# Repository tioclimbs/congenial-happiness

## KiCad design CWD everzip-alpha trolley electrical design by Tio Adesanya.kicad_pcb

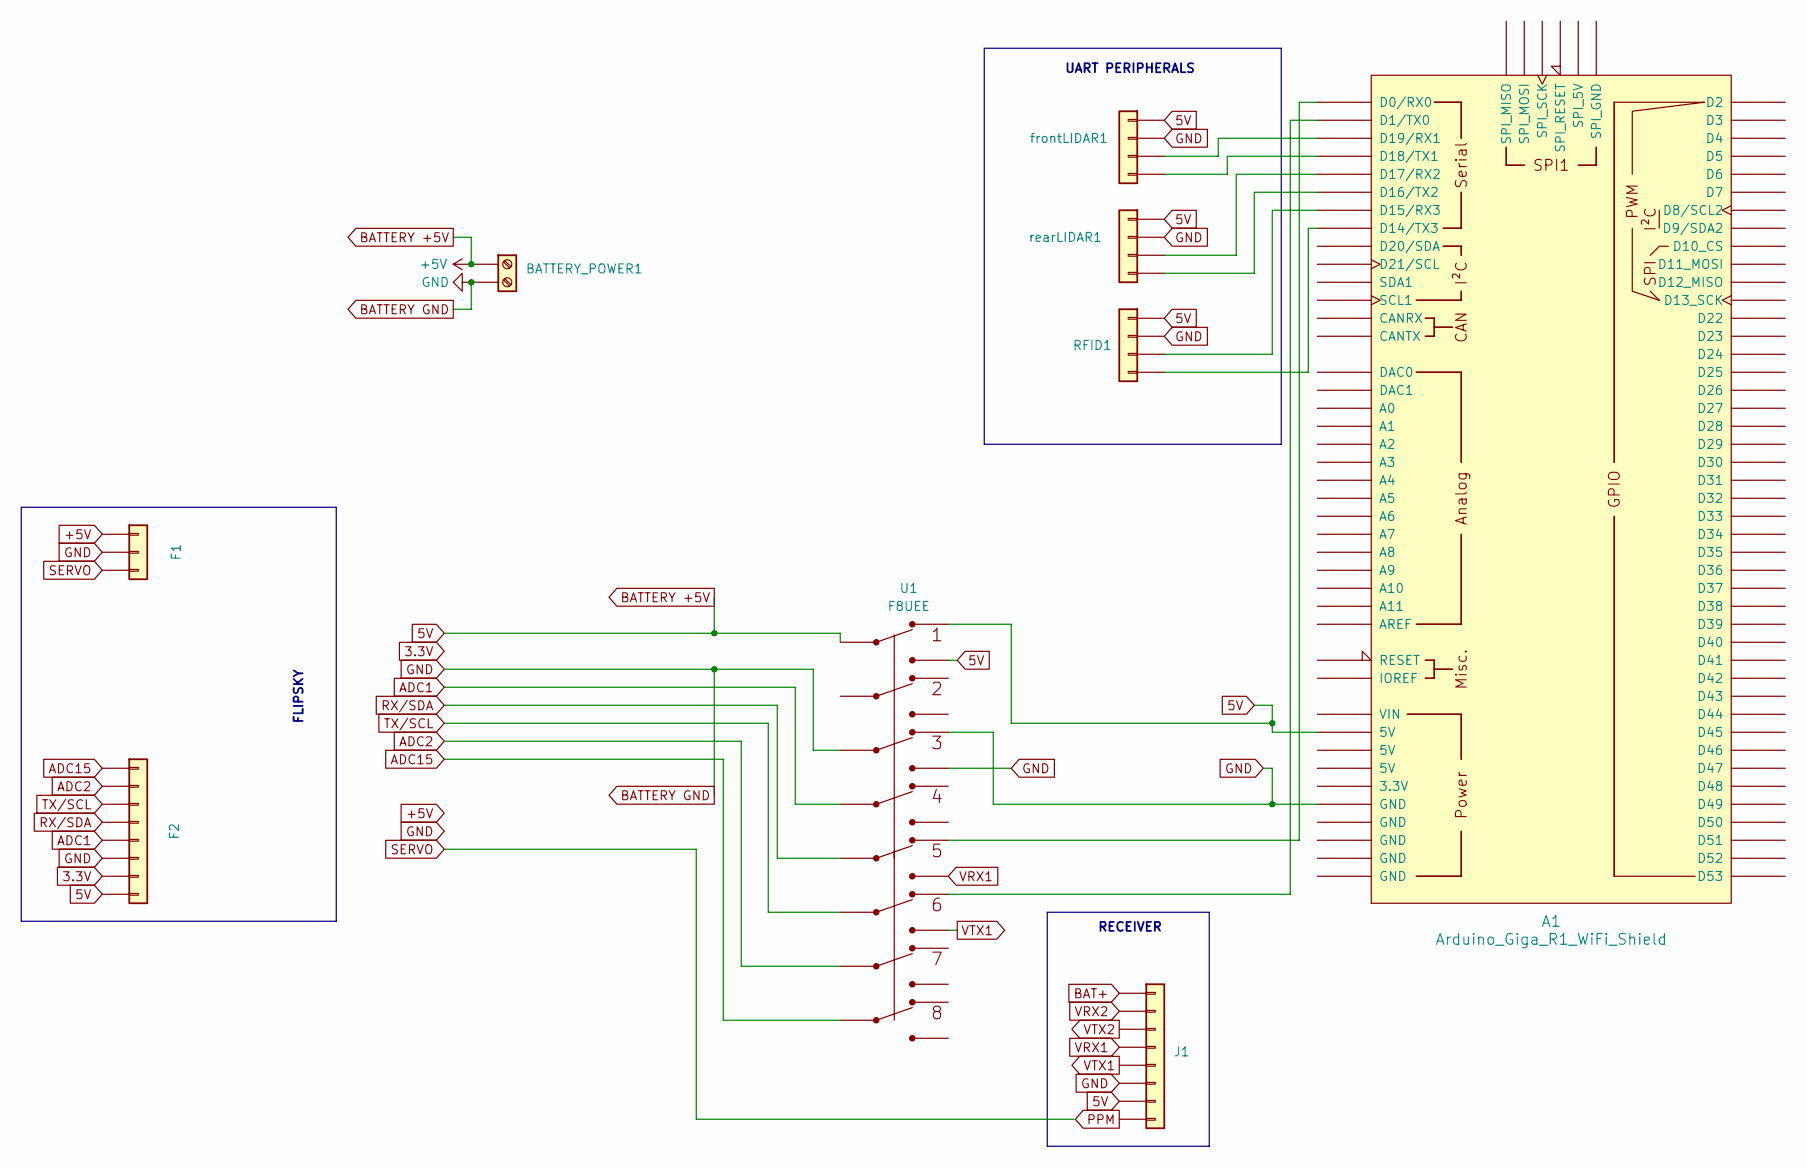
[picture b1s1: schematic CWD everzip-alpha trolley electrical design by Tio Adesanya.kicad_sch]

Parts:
A1: Arduino_Giga_R1_WiFi_Shield
BATTERY_POWER1: TerminalBlock_Phoenix_MKDS-1,5-2-5.08_1x02_P5.08mm_Horizont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
F1: PinHeader_1x03_P2.54mm_Vertical
F2: PinHeader_1x08_P2.54mm_Vertical
J1: PinHeader_1x08_P2.54mm_Vertical
RFID1: PinHeader_1x04_P2.54mm_Vertical
U1: F8UEE
frontLIDAR1: PinHeader_1x04_P2.54mm_Vertical
rearLIDAR1: PinHeader_1x04_P2.54mm_Vertical

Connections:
3.3V: F2.7
+5V: A1.5V1 (5V), BATTERY_POWER1.1, F1.1, F2.8, J1.7, RFID1.1, U1.1IN, U1.1OUT1, U1.1OUT2, frontLIDAR1.1, rearLIDAR1.1
ADC1: F2.5, U1.4IN
ADC2: F2.2, U1.7IN
ADC15: F2.1, U1.8IN
BAT+: J1.1
BATTERY GND: A1.GND1 (GND), BATTERY_POWER1.2, F1.2, F2.6, J1.6, RFID1.2, U1.3IN, U1.3OUT1, U1.3OUT2, frontLIDAR1.2, rearLIDAR1.2
unnamed: A1.D0 (D0/RX0), U1.5OUT1
unnamed: A1.D1 (D1/TX0), U1.6OUT1
unnamed: A1.D14 (D14/TX3), RFID1.4
unnamed: A1.D15 (D15/RX3), RFID1.3
unnamed: A1.D16 (D16/TX2), rearLIDAR1.4
unnamed: A1.D17 (D17/RX2), rearLIDAR1.3
unnamed: A1.D18 (D18/TX1), frontLIDAR1.4
unnamed: A1.D19 (D19/RX1), frontLIDAR1.3
PPM: J1.8
RX/SDA: F2.4, U1.5IN
SERVO: F1.3
TX/SCL: F2.3, U1.6IN
VRX1: J1.4, U1.5OUT2
VRX2: J1.2
VTX1: J1.5, U1.6OUT2
VTX2: J1.3

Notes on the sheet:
RECEIVER
FLIPSKY
UART PERIPHERALS

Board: 2 copper layers, 9 parts (0 on the bottom side), 17 nets, no tracks yet.

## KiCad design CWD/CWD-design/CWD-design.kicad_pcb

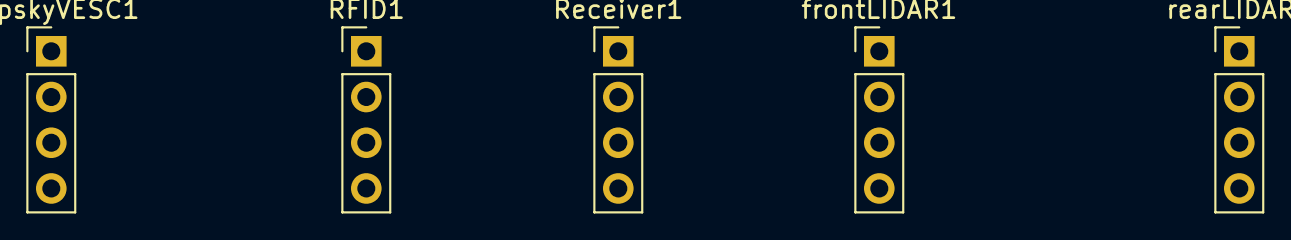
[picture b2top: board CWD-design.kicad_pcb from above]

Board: 2 copper layers, 5 parts (0 on the bottom side), 2 nets, no tracks yet.

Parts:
FlipskyVESC1: PinHeader_1x04_P2.54mm_Vertical
RFID1: PinHeader_1x04_P2.54mm_Vertical
Receiver1: PinHeader_1x04_P2.54mm_Vertical
frontLIDAR1: PinHeader_1x04_P2.54mm_Vertical
rearLIDAR1: PinHeader_1x04_P2.54mm_Vertical

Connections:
unnamed: RFID1.1, Receiver1.1, frontLIDAR1.1, rearLIDAR1.1
unnamed: RFID1.2, Receiver1.2, frontLIDAR1.2, rearLIDAR1.2

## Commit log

2025-07-29 Add files via upload
    initial commit
2025-07-30 Commit that works
    working commit
